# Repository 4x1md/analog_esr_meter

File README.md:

# ESR Meter

The schematic of this meter was published in an Italian magazine Nuova Elettronica No. 212.

## Overview

The schematic of this meter was published in an Italian magazine Nuova Elettronica No. 212. I found it more than five years ago on [Talino Tribuzio's IZ7ATH site](http://www.qsl.net/iz7ath/web/02_brew/15_lab/06_esr/index.htm) when I was looking for a simple ESR meter circuit.

## Reference circuits

```
R1 = 1.5K
R2,R3,R4,R5 = 10K
R6 = 68K
R7 = 4.7K
R8 = 12K
R9,R11 = 1K 1%
R10,R12 = 22 1%
R13,R14 = 1K
R15,R16,R17 = 47K
R18 = 15K
R19 = 680
R20 = 2.2K
R21 = 20K TRIMMER

C1,C2 = 1uF electrolytic
C3 = 1nF POLY
C4 = 100nFF POLY
C5,C6 = 1uF POLY
DS1, DS2 = 1N4007
DS3 = 1N4148
TR1,TR3 = BC547
TR2 = BC557
IC1 = TL084
```

## Project goals

1. Fitting the circuit in an enclosure box.
2. Dual power supply battery and external.

## Schematic

## Mechanics

A ready available 118x78x33mm plastic box which was purchased on AliExpress. The box is made of a good quality plastic, has enough space for the PCB and a battery compartment.

## PCB

## Assembled device

## Alignment

## Links
* http://fillwithgoodthings.blogspot.com/2013/05/esr-meter-schematic.html
* http://kripton2035.free.fr/analog%20esr/esr-poptronix.html
* http://electronics-diy.com/electronic_schematic.php?id=950
* http://www.geocities.jp/shoranosekai/ESR_Tester_Schematic.jpg
* http://ludens.cl/Electron/esr/esr.html
* http://electronics-diy.com/electronic_schematic.php?id=949

## How to Support or Say Thanks

If you like this project, or found here some useful information and want to say thanks, or encourage me to do more, you can buy me a coffee!

You can aslo make a donation with PayPal:

---

**73 de 4X1MD**

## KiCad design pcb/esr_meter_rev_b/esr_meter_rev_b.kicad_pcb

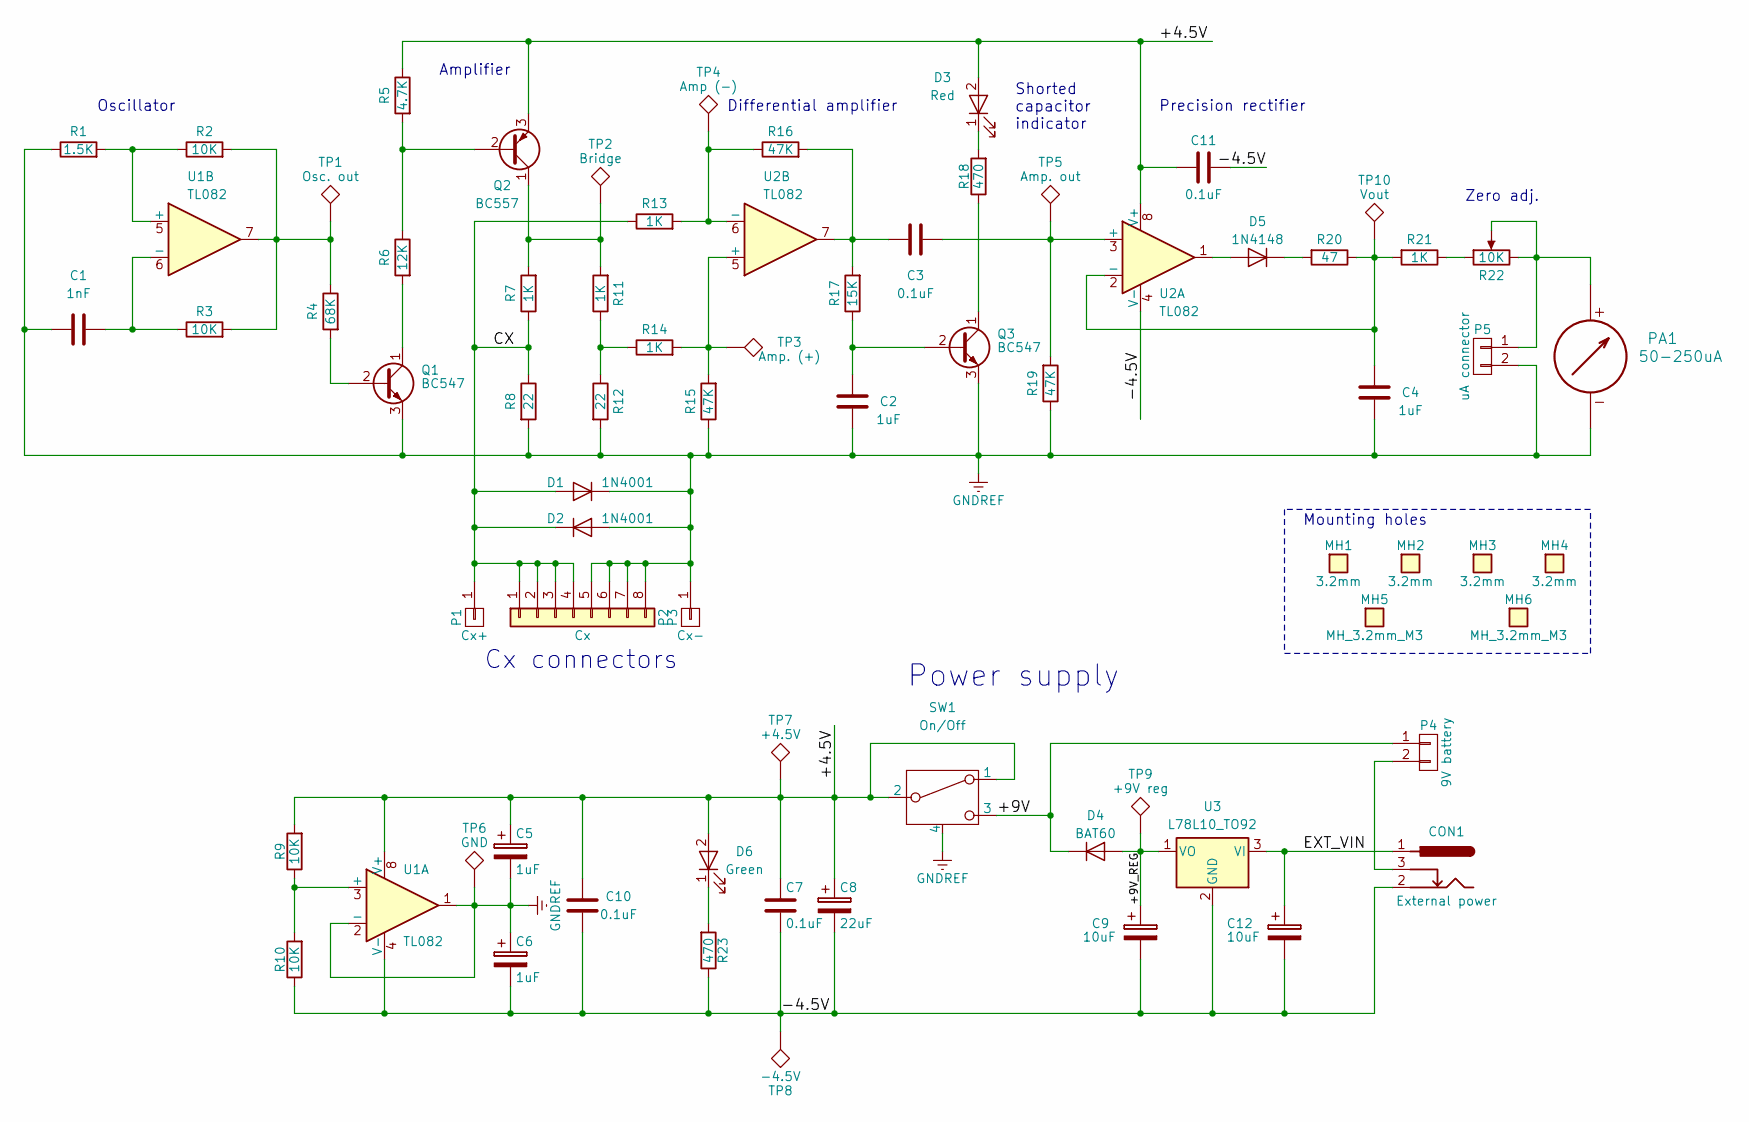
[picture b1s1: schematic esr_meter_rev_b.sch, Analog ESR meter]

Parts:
C1: 1nF; C_Rect_L7.0mm_W2.0mm_P5.00mm
C2, C4: 1uF; C_Rect_L7.0mm_W2.0mm_P5.00mm
C3, C7, C10, C11: 0.1uF; C_Rect_L7.0mm_W2.0mm_P5.00mm
C5, C6: 1uF; CP_Radial_D5.0mm_P2.50mm
C8: 22uF; CP_Radial_D5.0mm_P2.50mm
C9, C12: 10uF; CP_Radial_D5.0mm_P2.50mm
CON1: External power; BARREL_JACK_PCB_EDGE
D1, D2: 1N4001; D_DO-41_SOD81_P7.62mm_Horizontal
D3: Red; LED_D5.0mm
D4: BAT60; D_DO-35_SOD27_P7.62mm_Horizontal
D5: 1N4148; D_DO-35_SOD27_P5.08mm_Vertical_KathodeUp
D6: Green; LED_D5.0mm
MH1, MH2, MH3, MH4: 3.2mm; MountingHole_3.2mm_M3_Small
MH5, MH6: MH_3.2mm_M3; MountingHole_3.2mm_M3_DIN965
P1: Cx+; Banana_Jack_1Pin
P2: Cx; Socket_Strip_Straight_1x08_Pitch2.54mm
P3: Cx-; Banana_Jack_1Pin
P4: 9V battery; Pin_Header_Straight_1x02_Pitch2.54mm
P5: uA connector; Pin_Header_Straight_1x02_Pitch2.54mm
PA1: 50-250uA; Pin_Header_Straight_1x02_Pitch2.54mm
Q1, Q3: BC547; TO-92_Inline_Wide
Q2: BC557; TO-92_Inline_Wide
R1: 1.5K; R_Axial_DIN0207_L6.3mm_D2.5mm_P2.54mm_Vertical
R2, R3, R9, R10: 10K; R_Axial_DIN0207_L6.3mm_D2.5mm_P2.54mm_Vertical
R4: 68K; R_Axial_DIN0207_L6.3mm_D2.5mm_P2.54mm_Vertical
R5: 4.7K; R_Axial_DIN0207_L6.3mm_D2.5mm_P2.54mm_Vertical
R6: 12K; R_Axial_DIN0207_L6.3mm_D2.5mm_P2.54mm_Vertical
R7, R11, R13, R14, R21: 1K; R_Axial_DIN0207_L6.3mm_D2.5mm_P10.16mm_Horizontal
R8, R12: 22; R_Axial_DIN0207_L6.3mm_D2.5mm_P10.16mm_Horizontal
R15, R16: 47K; R_Axial_DIN0207_L6.3mm_D2.5mm_P10.16mm_Horizontal
R17: 15K; R_Axial_DIN0207_L6.3mm_D2.5mm_P10.16mm_Horizontal
R18, R23: 470; R_Axial_DIN0207_L6.3mm_D2.5mm_P10.16mm_Horizontal
R19: 47K; R_Axial_DIN0207_L6.3mm_D2.5mm_P2.54mm_Vertical
R20: 47; R_Axial_DIN0207_L6.3mm_D2.5mm_P10.16mm_Horizontal
R22: 10K; Potentiometer_Alps_RK09K_Horizontal
SW1: On/Off; Switch_Slide_SPDT_THT_5MS1S102AM6QES
TP1: Osc. out; Measurement_Point_Round-SMD-Pad_Small
TP2: Bridge; Measurement_Point_Round-SMD-Pad_Small
TP3: Amp. (+); Measurement_Point_Round-SMD-Pad_Small
TP4: Amp (-); Measurement_Point_Round-SMD-Pad_Small
TP5: Amp. out; Measurement_Point_Round-SMD-Pad_Small
TP6: GND; Measurement_Point_Round-SMD-Pad_Small
TP7: +4.5V; Measurement_Point_Round-SMD-Pad_Small
TP8: -4.5V; Measurement_Point_Round-SMD-Pad_Small
TP9: +9V reg; Measurement_Point_Round-SMD-Pad_Small
TP10: Vout; Measurement_Point_Round-SMD-Pad_Small
U1, U2: TL082; DIP-8_W7.62mm
U3: L78L10_TO92; TO-92_Inline_Wide

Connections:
/+4.5V: C5.1, C7.1, C8.1, C10.1, C11.1, D3.2 (A), D6.2 (A), Q2.3 (E), R5.1, R9.2, SW1.1, SW1.2, TP7.1, U1.8 (V+), U2.8 (V+); also elsewhere on the board
/+9V: D4.1 (K), P4.1, SW1.3
/+9V_REG: C9.1, D4.2 (A), TP9.1, U3.1 (VO)
/-4.5V: C6.2, C7.2, C8.2, C9.2, C10.2, C11.2, C12.2, CON1.2, R10.1, R23.1, TP8.1, U1.4 (V-), U2.4 (V-), U3.2 (GND)
/CX: D1.2 (A), D2.1 (K), P1.1, P2.1, P2.2, P2.3, P2.4, R7.1, R8.1, R13.1
/EXT_VIN: C12.1, CON1.1, U3.3 (VI)
GNDREF: C1.2, C2.2, C4.2, C5.2, C6.1, D1.1 (K), D2.2 (A), P2.5, P2.6, P2.7, P2.8, P3.1, P5.2, PA1.2 (-), Q1.3 (E), Q3.3 (E), R1.1, R8.2, R12.2, R15.1, R19.1, SW1.4, TP6.1, U1.1, U1.2 (-)
unnamed: C1.1, R3.1, U1.6 (-)
unnamed: C2.1, Q3.2 (B), R17.1
unnamed: C3.1, R16.2, R17.2, U2.7
unnamed: C3.2, R19.2, TP5.1, U2.3 (+)
unnamed: C4.1, R20.1, R21.2, TP10.1, U2.2 (-)
unnamed: CON1.3, P4.2
unnamed 13: D3.1 (K), R18.2; also elsewhere on the board
unnamed: D5.1 (K), R20.2
unnamed: D5.2 (A), U2.1
unnamed 16: D6.1 (K), R23.2; also elsewhere on the board
unnamed 17: P5.1, PA1.1 (+), R22.2, R22.3; also elsewhere on the board
unnamed: Q1.1 (C), R6.2
unnamed: Q1.2 (B), R4.2
unnamed: Q2.1 (C), R7.2, R11.2, TP2.1
unnamed: Q2.2 (B), R5.2, R6.1
unnamed: Q3.1 (C), R18.1
unnamed: R1.2, R2.1, U1.5 (+)
unnamed: R2.2, R3.2, R4.1, TP1.1, U1.7
unnamed: R9.1, R10.2, U1.3 (+)
unnamed: R11.1, R12.1, R14.1
unnamed: R13.2, R16.1, TP4.1, U2.6 (-)
unnamed: R14.2, R15.2, TP3.1, U2.5 (+)
unnamed 29: R21.1, R22.1; also elsewhere on the board

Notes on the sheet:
Power supply
Oscillator
Differential amplifier
Cx connectors
Amplifier
Shorted capacitor indicator
Zero adj.
Precision rectifier
Mounting holes

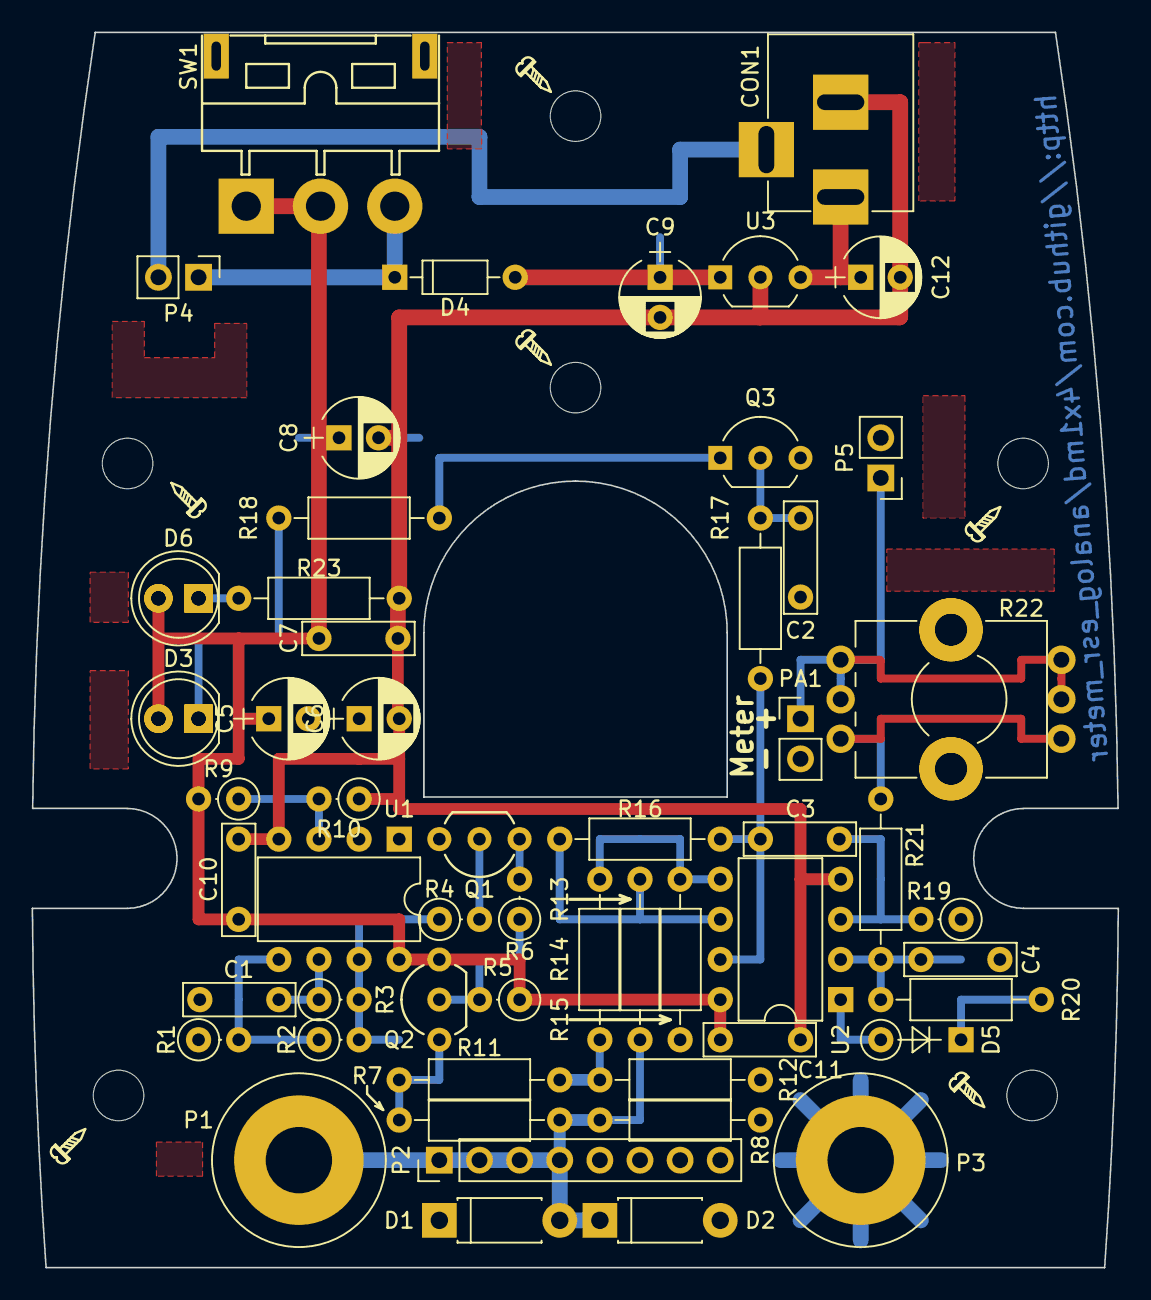
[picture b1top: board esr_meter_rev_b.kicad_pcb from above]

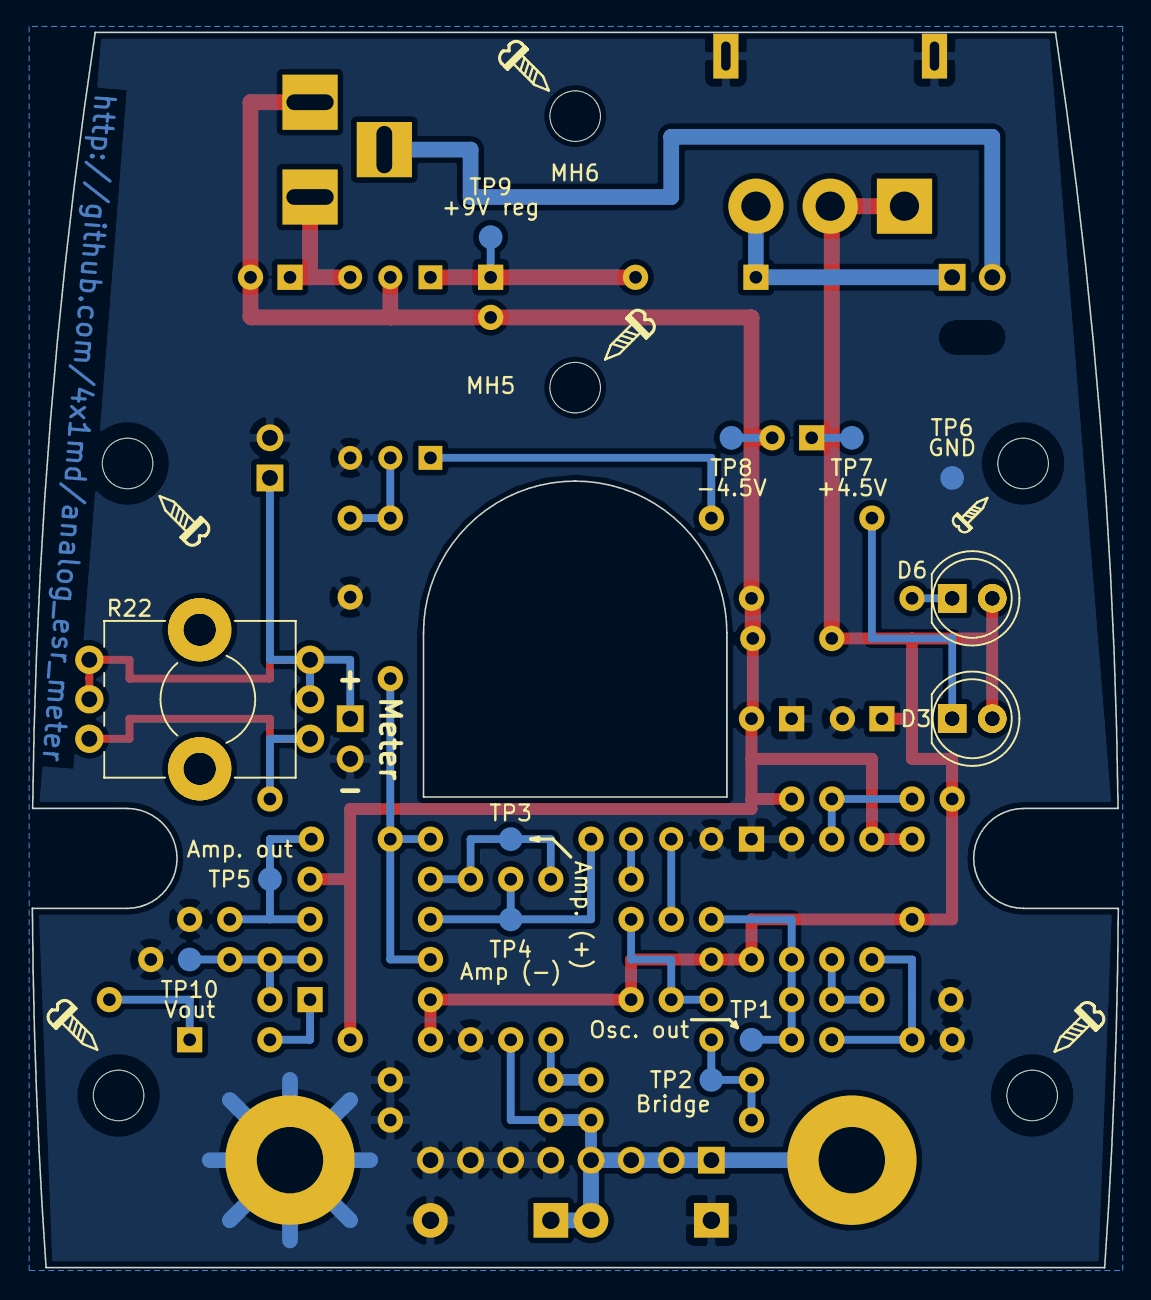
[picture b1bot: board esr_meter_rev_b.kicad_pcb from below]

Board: 2 copper layers, 68.7 x 78.2 mm, 75 parts (13 on the bottom side), 30 nets.

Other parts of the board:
D3#2: Red; LED_D5.0mm
D6#2: Green; LED_D5.0mm
MH**: 1.5mmx3.2mm_hole_for_wires
R22#2: 10K; Potentiometer_Alps_RK09K_Horizontal

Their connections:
/+4.5V: D3#2.2, D6#2.2; also elsewhere on the board
unnamed 13: D3#2.1; also elsewhere on the board
unnamed 16: D6#2.1; also elsewhere on the board
unnamed 17: R22#2.2, R22#2.3; also elsewhere on the board
unnamed 29: R22#2.1; also elsewhere on the board

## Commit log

2017-09-09 README.md: first commit.
2018-03-10 Images.
2018-03-10 PCB revision A.
2018-03-24 PCB mechanical drawing.
2018-04-07 LTspice simulations.
2018-09-01 Revison B: KiCAD 4.0 project and gerbers.
2018-09-29 Cosmetic changes to PCB.
2018-10-06 Corrected silkprints.
2019-01-25 Minor update.
